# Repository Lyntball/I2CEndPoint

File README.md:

# I2CEndPoint
I2C EndPointForHubs

This is the end point adapter for the I2C Hubs (logic level or multiplexer). With this device at the end point connected to a sensor or device, a distance of over 100 feet can be achived.

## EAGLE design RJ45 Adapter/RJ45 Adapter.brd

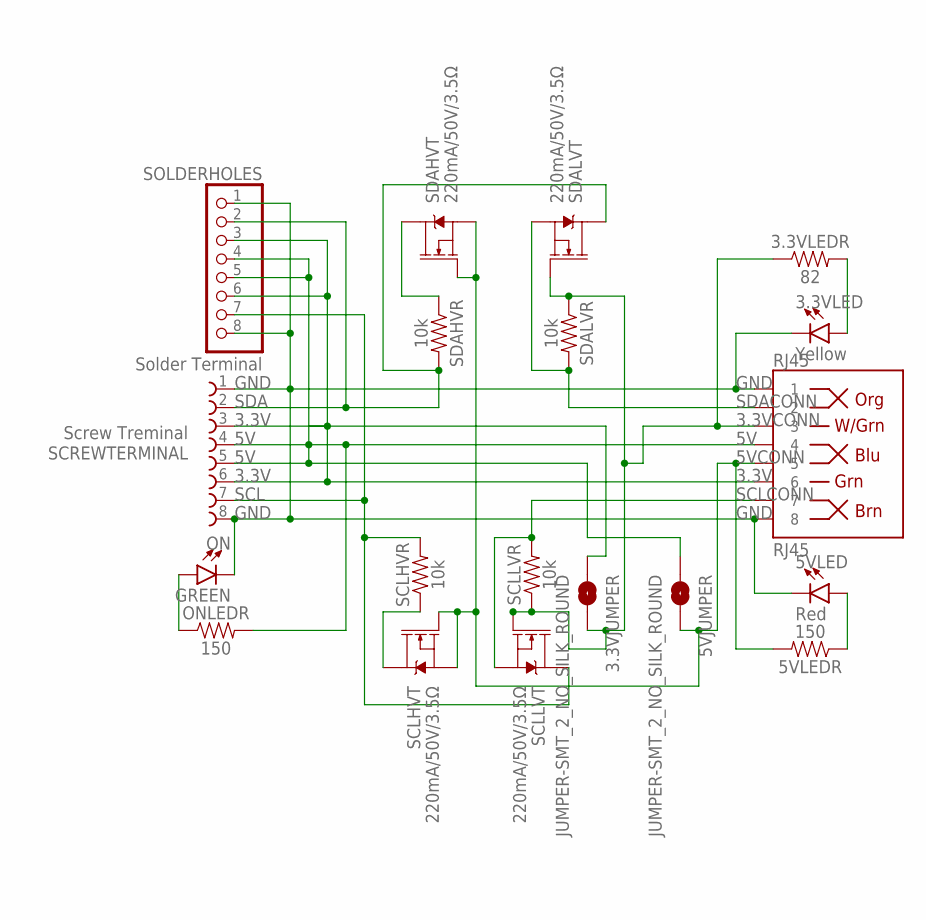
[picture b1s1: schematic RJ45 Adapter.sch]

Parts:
3.3VJUMPER, 5VJUMPER: JUMPER-SMT_2_NO_SILK_ROUND; SMT-JUMPER_2_NO_SILK_ROUND
3.3VLED: Yellow; LED-0603
3.3VLEDR: 82; 0603
5VLED: Red; LED-0603
5VLEDR: 150; 0603
ON: GREEN; LED-0603
ONLEDR: 150; 0603
RJ45: RJ45; RJ45-8
SCLHVR: 10k; 0603
SCLHVT: 220mA/50V/3.5Ω; SOT23-3
SCLLVR: 10k; 0603
SCLLVT: 220mA/50V/3.5Ω; SOT23-3
SCREWTERMINAL: Screw Treminal; 691243300008
SDAHVR: 10k; 0603
SDAHVT: 220mA/50V/3.5Ω; SOT23-3
SDALVR: 10k; 0603
SDALVT: 220mA/50V/3.5Ω; SOT23-3
SOLDERHOLES: Solder Terminal; 1X08-3.5MM

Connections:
3.3LEDR: 3.3VLED.A, 3.3VLEDR.2
3.3V: 3.3VJUMPER.1, RJ45.6, SCREWTERMINAL.3 (6), SCREWTERMINAL.6 (3), SOLDERHOLES.3, SOLDERHOLES.6
3.3VCONN: 3.3VJUMPER.2, 3.3VLEDR.1, RJ45.3, SCLLVR.1, SCLLVT.1 (G), SDALVR.1, SDALVT.1 (G)
5V: 5VJUMPER.1, ONLEDR.2, RJ45.4, SCREWTERMINAL.4 (5), SCREWTERMINAL.5 (4), SOLDERHOLES.4, SOLDERHOLES.5
5VCONN: 5VJUMPER.2, 5VLEDR.2, RJ45.5, SCLHVT.1 (G), SCLHVT.2 (S), SDAHVT.1 (G), SDAHVT.2 (S)
5VLEDR: 5VLED.A, 5VLEDR.1
GND: 3.3VLED.C, 5VLED.C, ON.C, RJ45.1, RJ45.8, SCREWTERMINAL.1 (8), SCREWTERMINAL.8 (1), SOLDERHOLES.1, SOLDERHOLES.8
ONLEDR: ON.A, ONLEDR.1
SCL: SCLHVR.2, SCLLVT.3 (D), SCREWTERMINAL.7 (2), SOLDERHOLES.7
SCLCONN: RJ45.7, SCLLVR.2, SCLLVT.2 (S)
SCLHV: SCLHVR.1, SCLHVT.3 (D)
SDA: SCREWTERMINAL.2 (7), SDAHVR.2, SDALVT.3 (D), SOLDERHOLES.2
SDACONN: RJ45.2, SDALVR.2, SDALVT.2 (S)
SDAHV: SDAHVR.1, SDAHVT.3 (D)

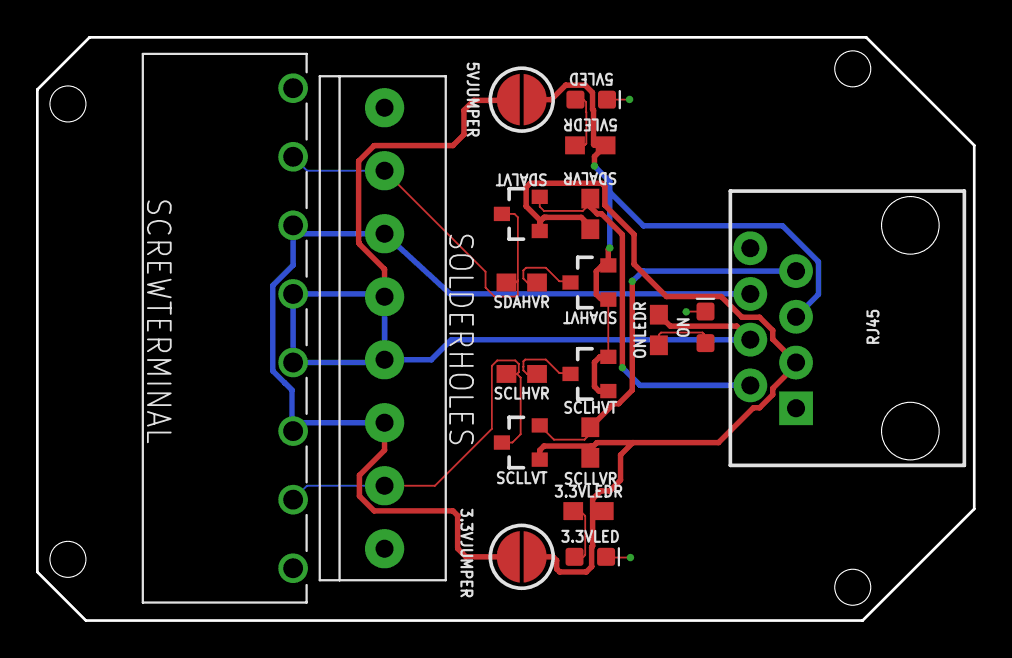
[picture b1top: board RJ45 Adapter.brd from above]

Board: 2 copper layers, 52.0 x 32.4 mm, 19 parts (0 on the bottom side), 14 nets.

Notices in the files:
parts and their libraries:
SparkFun-Jumpers: Licensing: Creative Commons ShareAlike 4.0 International - https://creativecommons.org/licenses/by-sa/4.0
Wurth_Elektronik_Electromechanic_Termina: Copyright: Würth Elektronik
